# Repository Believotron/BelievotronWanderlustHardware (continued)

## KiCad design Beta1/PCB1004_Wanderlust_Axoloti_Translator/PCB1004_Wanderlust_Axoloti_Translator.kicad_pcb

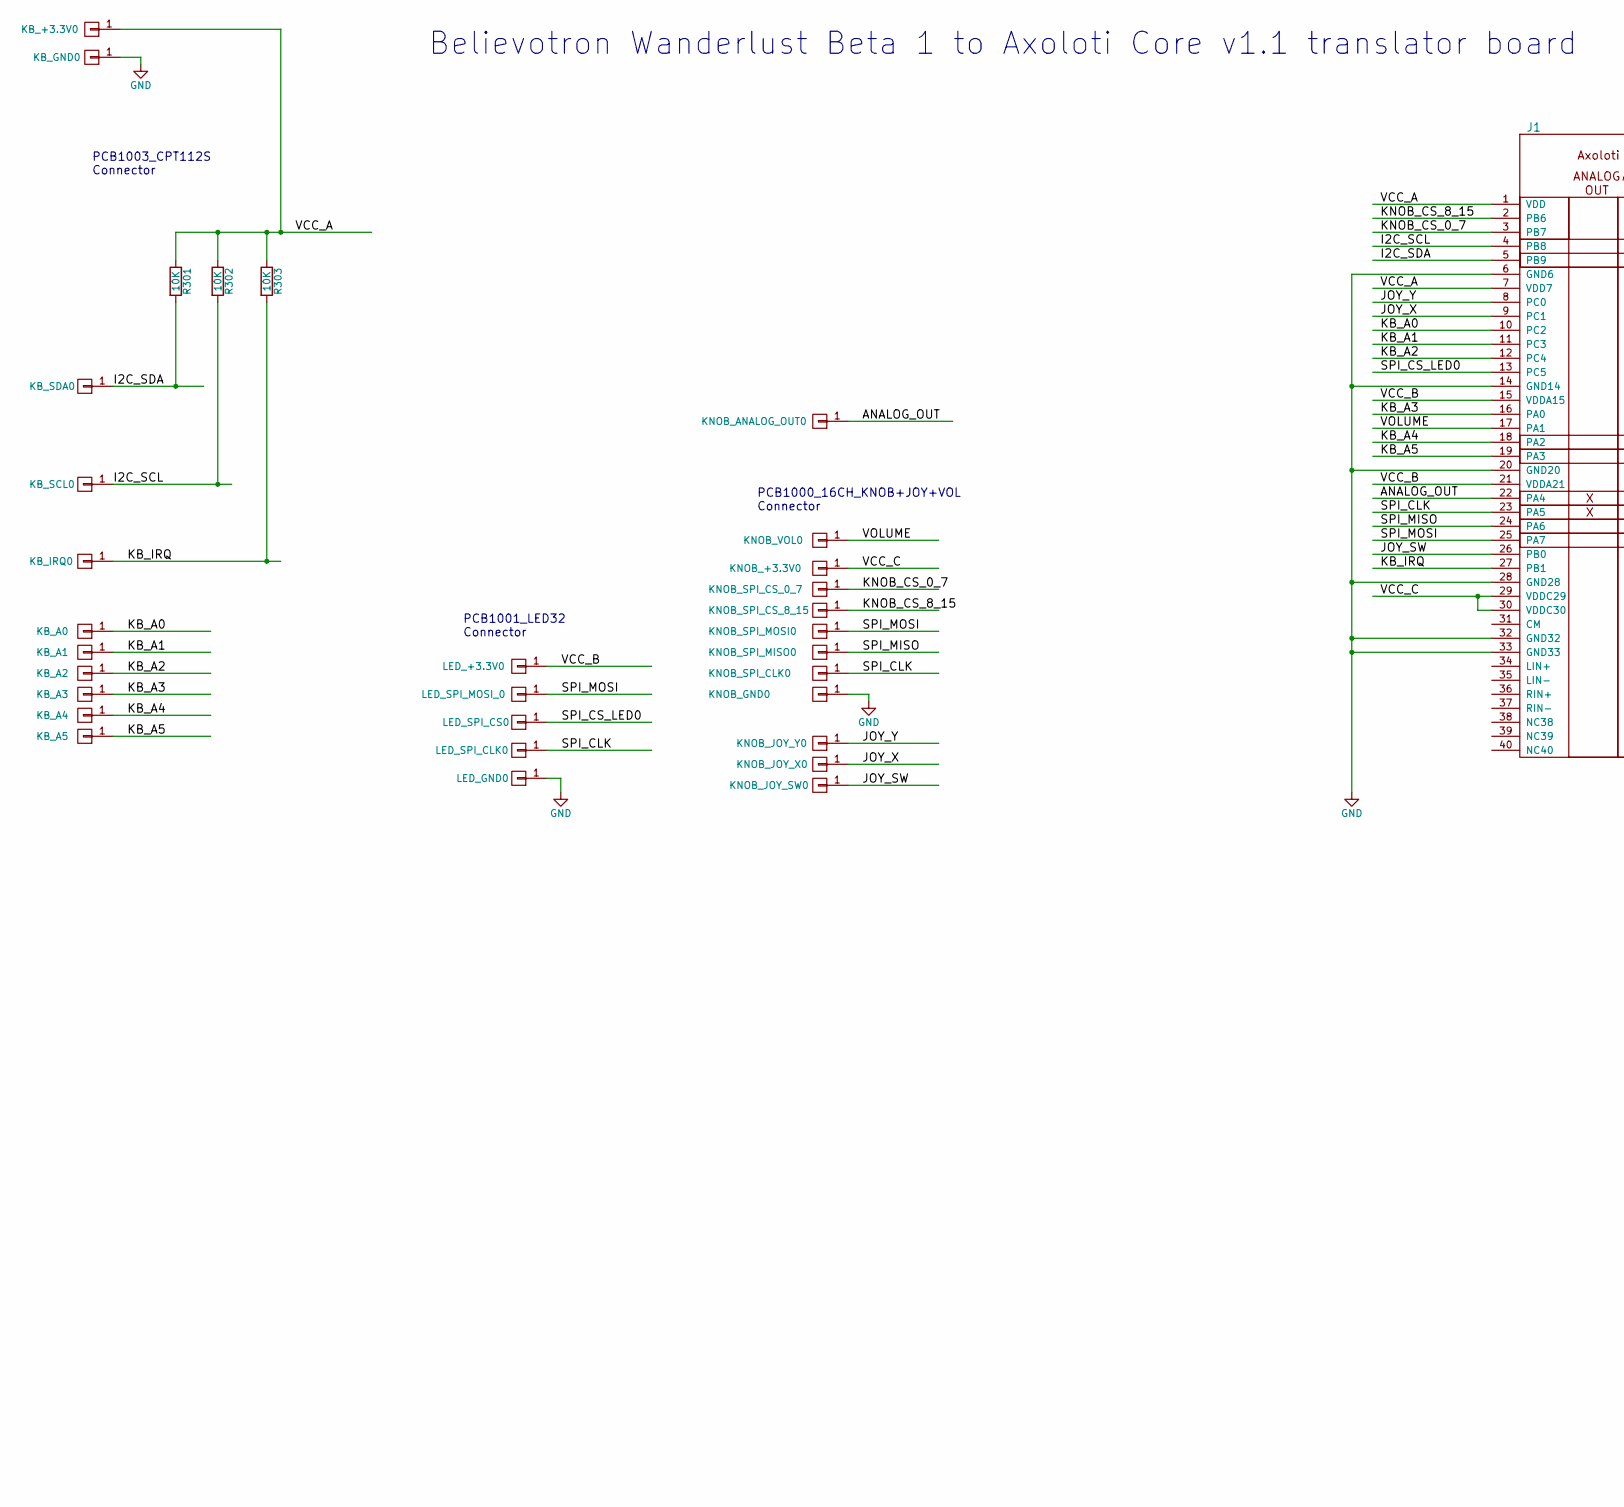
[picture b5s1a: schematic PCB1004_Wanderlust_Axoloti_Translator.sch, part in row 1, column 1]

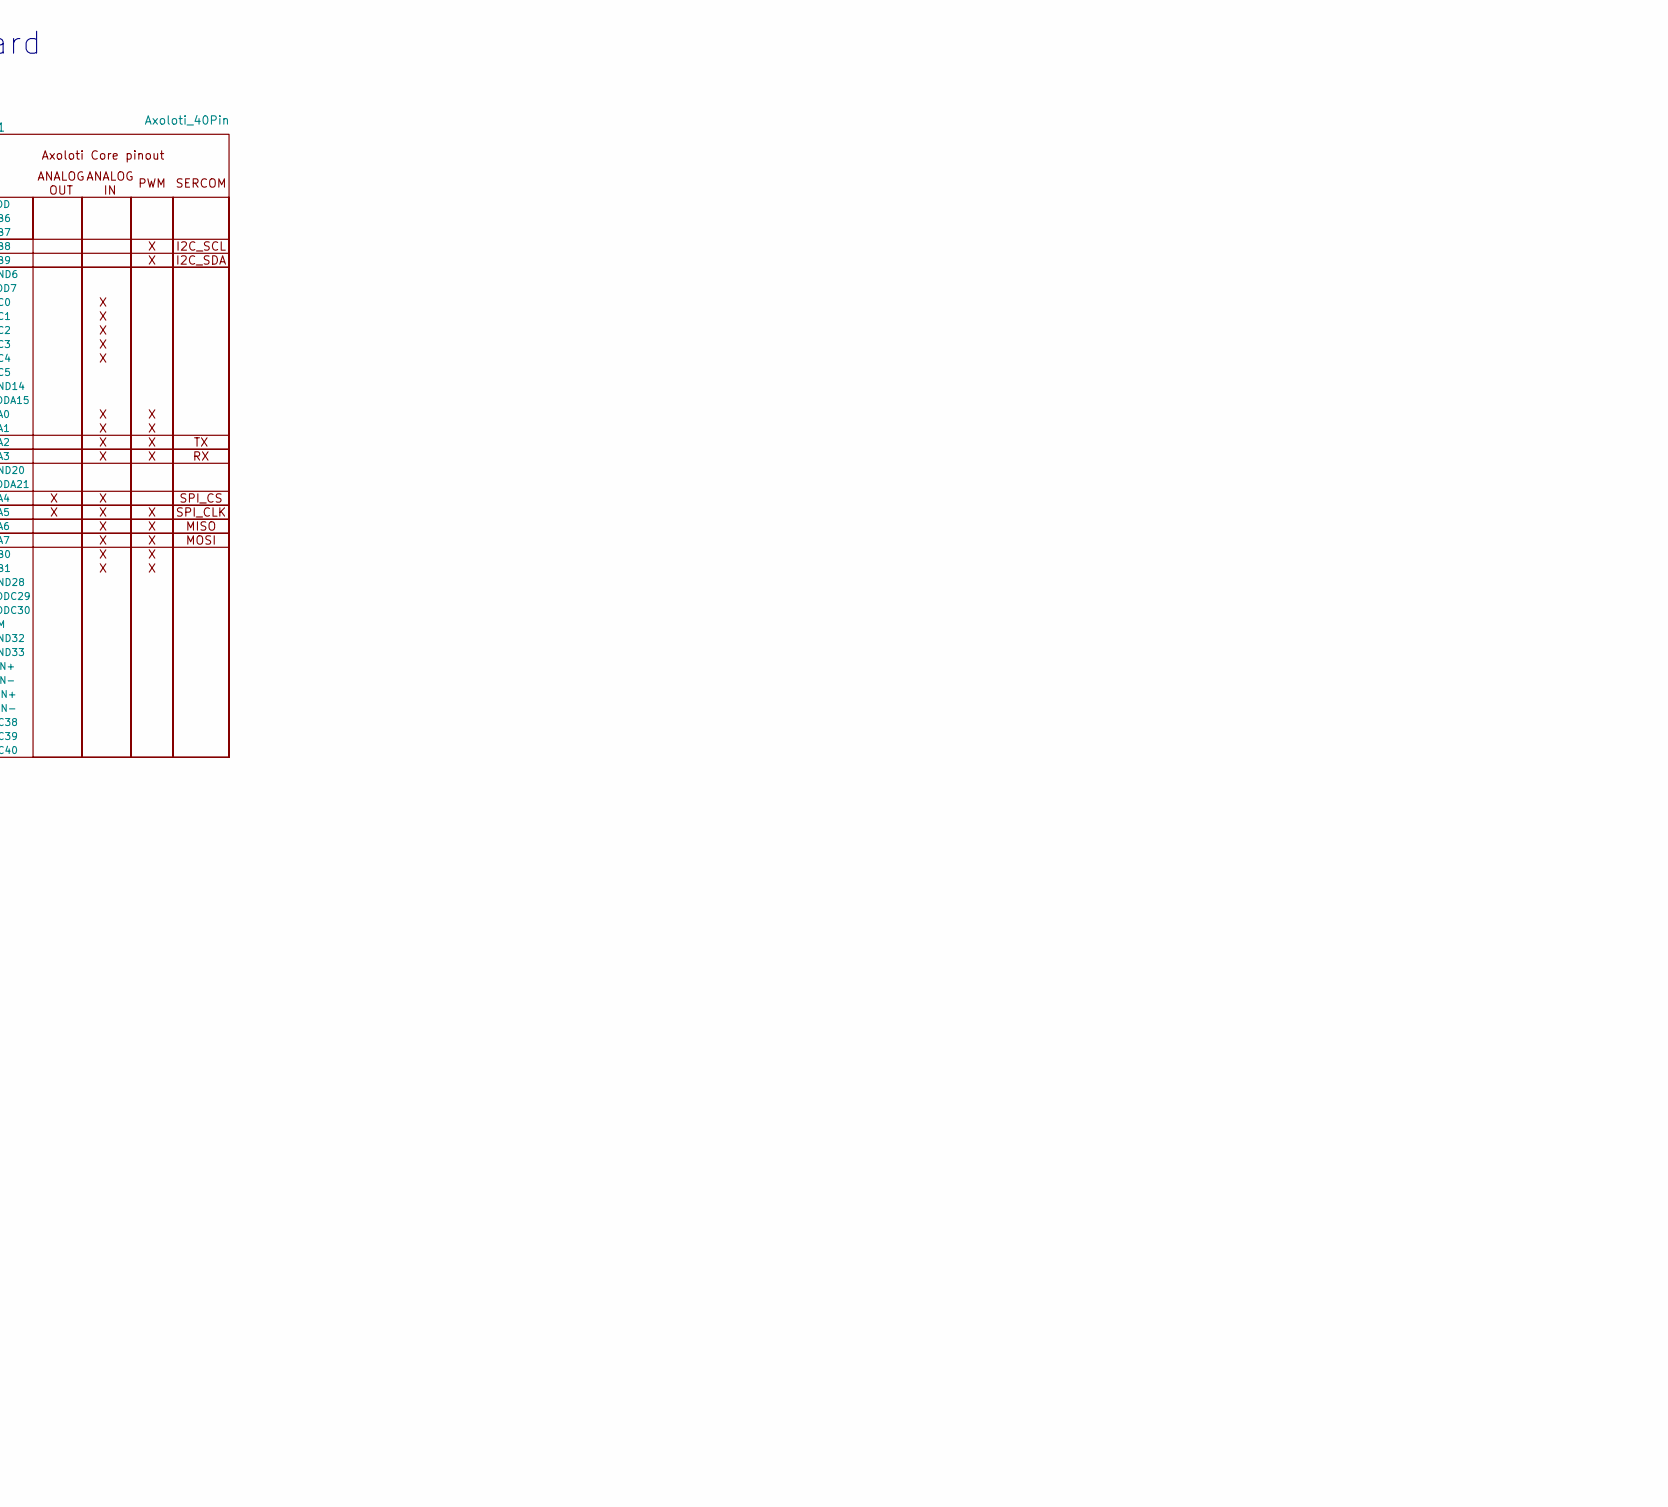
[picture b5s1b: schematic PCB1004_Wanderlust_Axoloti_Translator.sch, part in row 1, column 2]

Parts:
J1: Axoloti_40Pin; Axoloti-40x3
KB_+3.3V0: CONN_01X01; TH_0.1_1x2_Jumper; MPN ON_PCB
KB_A0, KB_A1, KB_A2, KB_A3, KB_A4, KB_A5: CONN_01X01; TH_0.1_1x2_Jumper; MPN ON_PCB
KB_GND0: CONN_01X01; TH_0.1_1x2_Jumper; MPN ON_PCB
KB_IRQ0: CONN_01X01; TH_0.1_1x2_Jumper; MPN ON_PCB
KB_SCL0: CONN_01X01; TH_0.1_1x2_Jumper; MPN ON_PCB
KB_SDA0: CONN_01X01; TH_0.1_1x2_Jumper; MPN ON_PCB
KNOB_+3.3V0: CONN_01X01; TH_0.1_1x2_Jumper; MPN ON_PCB
KNOB_ANALOG_OUT0: CONN_01X01; TH_0.1_1x2_Jumper; MPN ON_PCB
KNOB_GND0: CONN_01X01; TH_0.1_1x2_Jumper; MPN ON_PCB
KNOB_JOY_SW0: CONN_01X01; TH_0.1_1x2_Jumper; MPN ON_PCB
KNOB_JOY_X0: CONN_01X01; TH_0.1_1x2_Jumper; MPN ON_PCB
KNOB_JOY_Y0: CONN_01X01; TH_0.1_1x2_Jumper; MPN ON_PCB
KNOB_SPI_CLK0: CONN_01X01; TH_0.1_1x2_Jumper; MPN ON_PCB
KNOB_SPI_CS_0_7, KNOB_SPI_CS_8_15: CONN_01X01; TH_0.1_1x2_Jumper; MPN ON_PCB
KNOB_SPI_MISO0: CONN_01X01; TH_0.1_1x2_Jumper; MPN ON_PCB
KNOB_SPI_MOSI0: CONN_01X01; TH_0.1_1x2_Jumper; MPN ON_PCB
KNOB_VOL0: CONN_01X01; TH_0.1_1x2_Jumper; MPN ON_PCB
LED_+3.3V0: CONN_01X01; TH_0.1_1x2_Jumper; MPN ON_PCB
LED_GND0: CONN_01X01; TH_0.1_1x2_Jumper; MPN ON_PCB
LED_SPI_CLK0: CONN_01X01; TH_0.1_1x2_Jumper; MPN ON_PCB
LED_SPI_CS0: CONN_01X01; TH_0.1_1x2_Jumper; MPN ON_PCB
LED_SPI_MOSI_0: CONN_01X01; TH_0.1_1x2_Jumper; MPN ON_PCB
R301, R302, R303: 10K; R_0603; MPN CRCW060310K0JNEA

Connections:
/ANALOG_OUT: J1.22 (PA4), KNOB_ANALOG_OUT0.1
/I2C_SCL: J1.4 (PB8), KB_SCL0.1, R302.2
/I2C_SDA: J1.5 (PB9), KB_SDA0.1, R301.2
/JOY_SW: J1.26 (PB0), KNOB_JOY_SW0.1
/JOY_X: J1.9 (PC1), KNOB_JOY_X0.1
/JOY_Y: J1.8 (PC0), KNOB_JOY_Y0.1
/KB_A0: J1.10 (PC2), KB_A0.1
/KB_A1: J1.11 (PC3), KB_A1.1
/KB_A2: J1.12 (PC4), KB_A2.1
/KB_A3: J1.16 (PA0), KB_A3.1
/KB_A4: J1.18 (PA2), KB_A4.1
/KB_A5: J1.19 (PA3), KB_A5.1
/KB_IRQ: J1.27 (PB1), KB_IRQ0.1, R303.2
/KNOB_CS_0_7: J1.3 (PB7), KNOB_SPI_CS_0_7.1
/KNOB_CS_8_15: J1.2 (PB6), KNOB_SPI_CS_8_15.1
/SPI_CLK: J1.23 (PA5), KNOB_SPI_CLK0.1, LED_SPI_CLK0.1
/SPI_CS_LED0: J1.13 (PC5), LED_SPI_CS0.1
/SPI_MISO: J1.24 (PA6), KNOB_SPI_MISO0.1
/SPI_MOSI: J1.25 (PA7), KNOB_SPI_MOSI0.1, LED_SPI_MOSI_0.1
/VCC_A: J1.1 (VDD), J1.7 (VDD7), KB_+3.3V0.1, R301.1, R302.1, R303.1
/VCC_B: J1.15 (VDDA15), J1.21 (VDDA21), LED_+3.3V0.1
/VCC_C: J1.29 (VDDC29), J1.30 (VDDC30), KNOB_+3.3V0.1
/VOLUME: J1.17 (PA1), KNOB_VOL0.1
GND: J1.6 (GND6), J1.14 (GND14), J1.20 (GND20), J1.28 (GND28), J1.32 (GND32), J1.33 (GND33), KB_GND0.1, KNOB_GND0.1, LED_GND0.1

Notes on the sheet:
Open source MIT license files at: github.com/Believotron/BelievotronWanderlustHardware Replacement parts, upgrades, updates, new gear, and marketing pap: Believotron.com For help, bug reporting, dev-blogs, or joy at your bonkers-cool creation, the good stuff is here: community.believotron.com
2017-03-31
DATE
Believotron Wanderlust Beta1 to Axoloti v1.1 translator PCB
PCB1003_CPT112S Connector
PCB1001_LED32 Connector
PCB1000_16CH_KNOB+JOY+VOL Connector
Believotron Wanderlust Beta 1 to Axoloti Core v1.1 translator board

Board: 2 copper layers, 32 parts (0 on the bottom side), 24 nets, no tracks yet.
